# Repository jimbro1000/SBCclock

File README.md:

# Clock Card for HD6309SBC #

This board provides a variety of divided clock signals
to the 6809SBC board.

Where the SBC board calls for a quadrature clock (for
the 6809E variants) the board also provides Q and E.

The design is intended to be swappable to permit
easy exchange of different clock rates or different
clock generator designs.

The intended target is a raw clock of 25.175MHz to
facilitate a VGA signal. The CPU then operates at
one eighth of that - 3.15MHz, slightly above the
expected clock maximum for a C-class processor but
well within tolerance.

By having a swappable clock card the target 
operating frequency can be halved again to allow
the use of B-class processors while retaining
the 25MHz VGA signal. Again this is slightly
above specification at 1.57MHz but within the
tolerance of the design.

## Outputs ##

The card must provide the raw clock on Clock24, this
can be any frequency (that the CPUs support) but 
changing from the VGA clock frequency will require a
different approach to video output.

Outputs are then expected for the clock divided by
2, 4, 8 and 16 (Clock12, Clock6, Clock3 and Clock1.5)

Where Q and E are used they are output along with the
inverse of each.

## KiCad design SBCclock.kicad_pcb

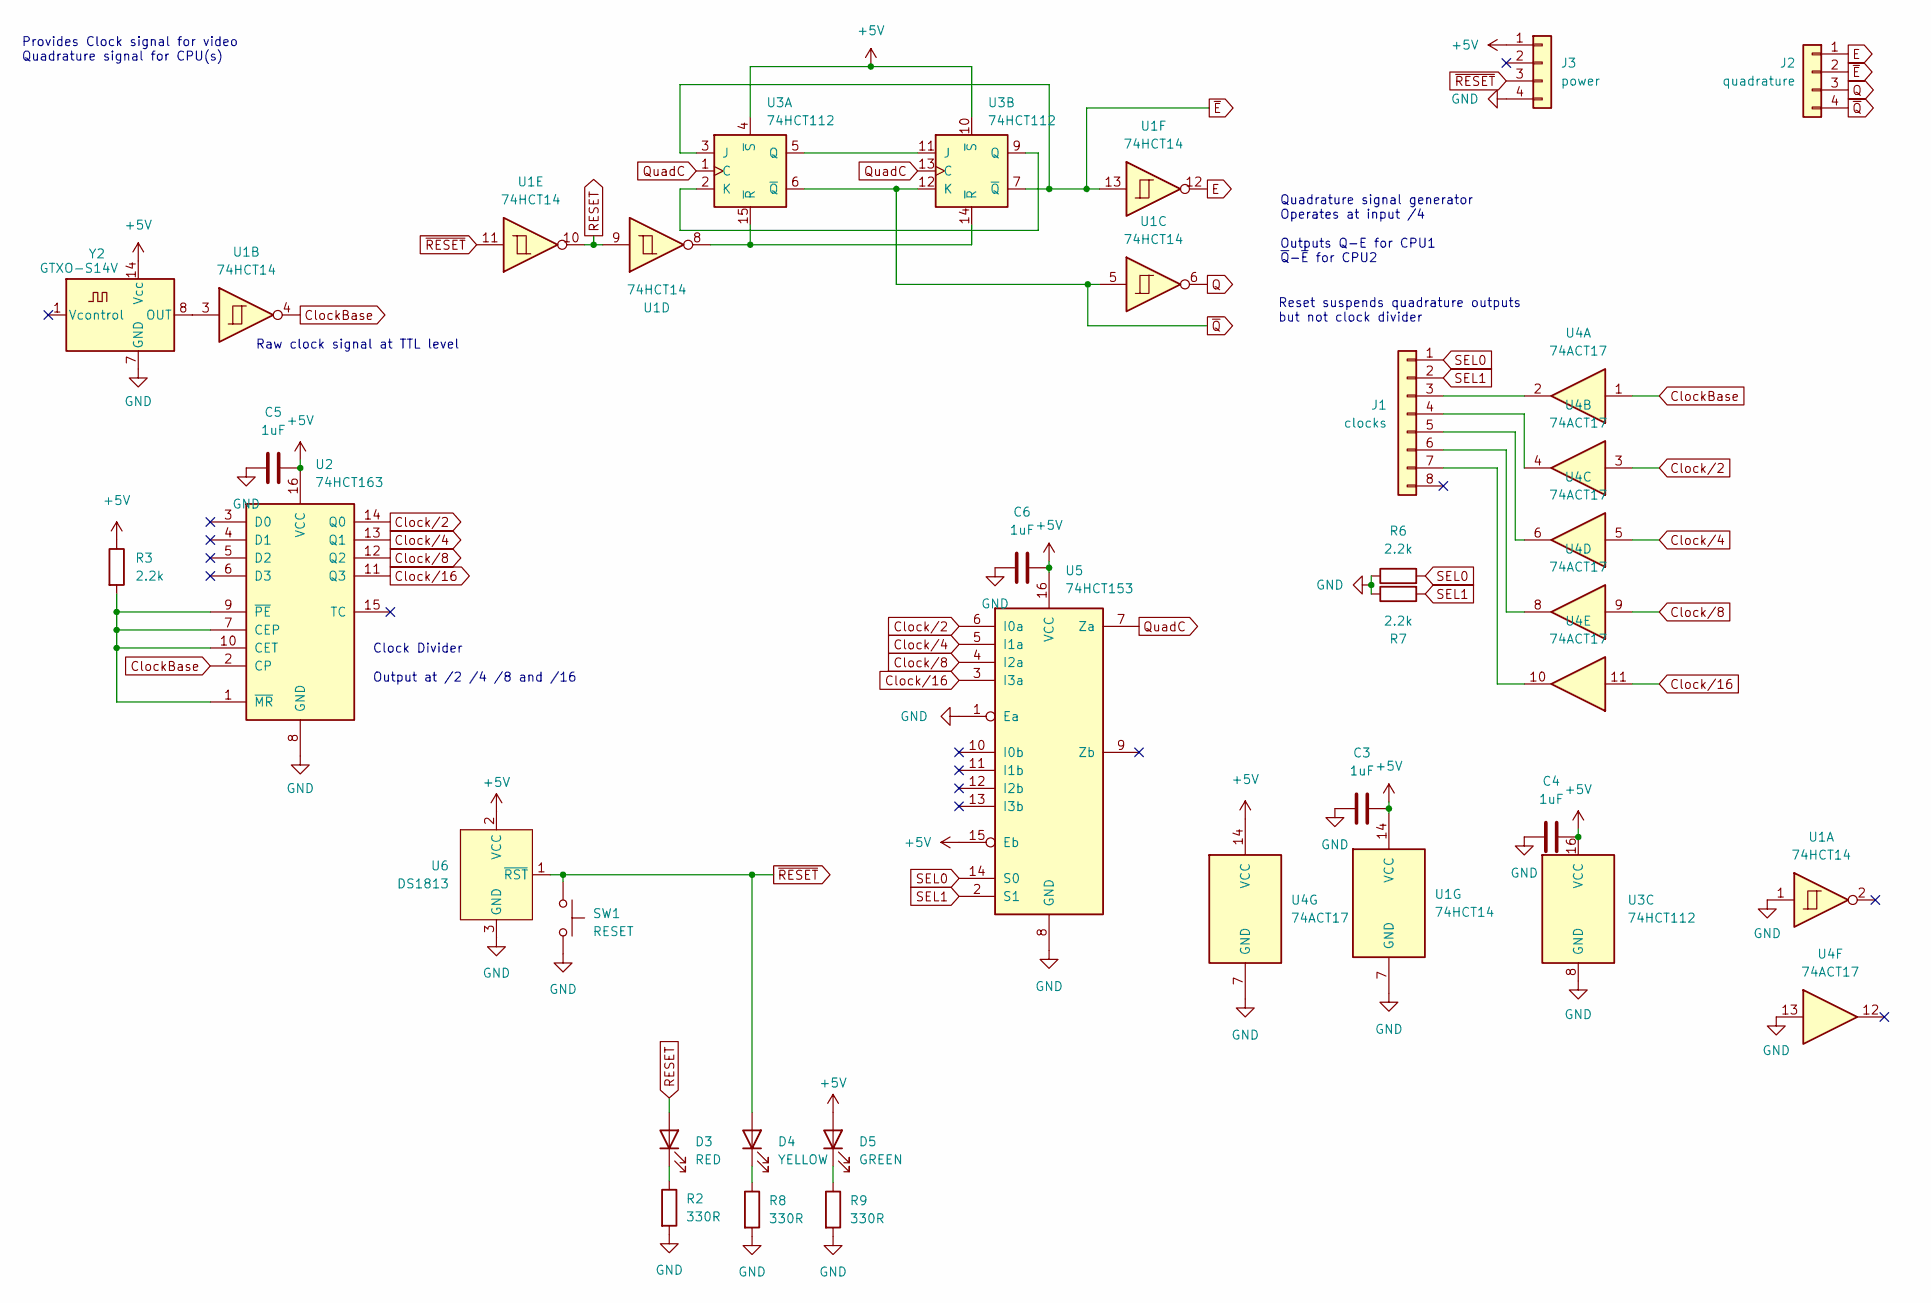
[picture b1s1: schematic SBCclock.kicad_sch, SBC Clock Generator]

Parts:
C3, C4, C5, C6: 1uF; C_0805_2012Metric_Pad1.18x1.45mm_HandSolder; DigiKey 4363-0805N180FW251XCT-ND
D3: RED; LED_0805_2012Metric_Pad1.15x1.40mm_HandSolder
D4: YELLOW; LED_0805_2012Metric_Pad1.15x1.40mm_HandSolder
D5: GREEN; LED_0805_2012Metric_Pad1.15x1.40mm_HandSolder
J1: clocks; PinHeader_1x08_P2.54mm_Vertical
J2: quadrature; PinHeader_1x04_P2.54mm_Vertical
J3: power; PinHeader_1x04_P2.54mm_Vertical
R2, R8, R9: 330R; R_0805_2012Metric_Pad1.20x1.40mm_HandSolder; DigiKey 2019-RK73H2ATTD2201FCT-ND
R3, R6, R7: 2.2k; R_0805_2012Metric_Pad1.20x1.40mm_HandSolder; DigiKey 2019-RK73H2ATTD2201FCT-ND
SW1: RESET; SW_SPST_B3S-1000
U1: 74HCT14; SOIC-14_3.9x8.7mm_P1.27mm; DigiKey 296-14864-1-ND
U2: 74HCT163; SOIC-16_3.9x9.9mm_P1.27mm; DigiKey 296-SN74HC163DTCT-ND
U3: 74HCT112; SOIC-16_3.9x9.9mm_P1.27mm; DigiKey 1727-74HCT112D,653CT-ND
U4: 74ACT17; TSSOP-14_4.4x5mm_P0.65mm; DigiKey 296-SN74ACT17PWRCT-ND
U5: 74HCT153; SOIC-16_3.9x9.9mm_P1.27mm; DigiKey 296-CD74HCT153M96CT-ND
U6: DS1813; SOT-23-3; DigiKey DS1813R-5+CT-ND
Y2: GTXO-S14V; Oscillator_DIP-8+14

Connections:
+5V: C3.1, C4.1, C5.1, C6.1, D5.2 (A), J3.1, R3.1, U1.14 (VCC), U2.16 (VCC), U3.4 (~S), U3.10 (~S), U3.16 (VCC), U4.14 (VCC), U5.15 (Eb), U5.16 (VCC), U6.2 (VCC), Y2.14 (Vcc)
ClockBase: U1.4, U2.2 (CP), U4.1
Clock/2: U2.14 (Q0), U4.3, U5.6 (I0a)
Clock/4: U2.13 (Q1), U4.5, U5.5 (I1a)
Clock/8: U2.12 (Q2), U4.9, U5.4 (I2a)
Clock/16: U2.11 (Q3), U4.11, U5.3 (I3a)
E: J2.1, U1.12
GND: C3.2, C4.2, C5.2, C6.2, J3.4, R2.2, R6.1, R7.1, R8.2, R9.2, SW1.2, U1.1, U1.7 (GND), U2.8 (GND), U3.8 (GND), U4.7 (GND), U4.13, U5.1 (Ea), U5.8 (GND), U6.3 (GND), Y2.7 (GND)
unnamed: D3.1 (K), R2.1
unnamed: D4.1 (K), R8.1
unnamed: D5.1 (K), R9.1
unnamed: J1.3, U4.2
unnamed: J1.4, U4.4
unnamed: J1.5, U4.6
unnamed: J1.6, U4.8
unnamed: J1.7, U4.10
unnamed: R3.2, U2.1 (~MR), U2.7 (CEP), U2.9 (~PE), U2.10 (CET)
unnamed: U3.2 (K), U3.9 (Q)
unnamed: U3.5 (Q), U3.11 (J)
unnamed: U1.8, U3.14 (~R), U3.15 (~R)
unnamed: U1.3, Y2.8 (OUT)
Q: J2.3, U1.6
QuadC: U3.1 (C), U3.13 (C), U5.7 (Za)
RESET: D3.2 (A), U1.9, U1.10
SEL0: J1.1, R6.2, U5.14 (S0)
SEL1: J1.2, R7.2, U5.2 (S1)
~E: J2.2, U1.13, U3.3 (J), U3.7 (~Q)
~Q: J2.4, U1.5, U3.6 (~Q), U3.12 (K)
~RESET: D4.2 (A), J3.3, SW1.1, U1.11, U6.1 (~RST)

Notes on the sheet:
Clock Divider Output at /2 /4 /8 and /16
Quadrature signal generator Operates at input /4 Outputs Q-E for CPU1 ~{Q}-~{E} for CPU2
Provides Clock signal for video Quadrature signal for CPU(s)
Reset suspends quadrature outputs but not clock divider
Raw clock signal at TTL level

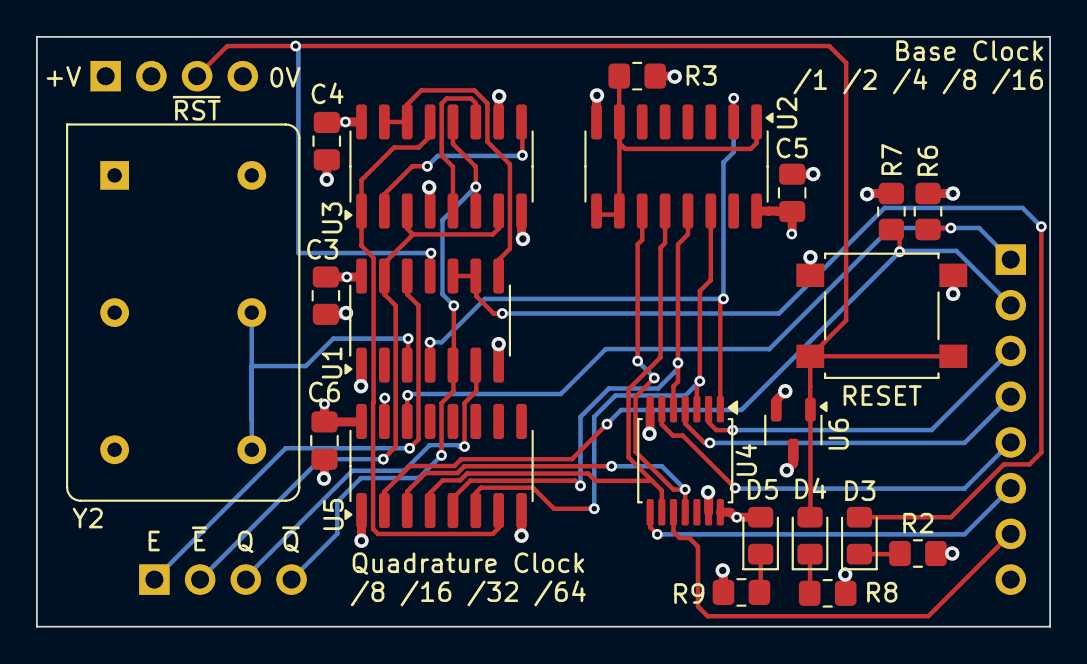
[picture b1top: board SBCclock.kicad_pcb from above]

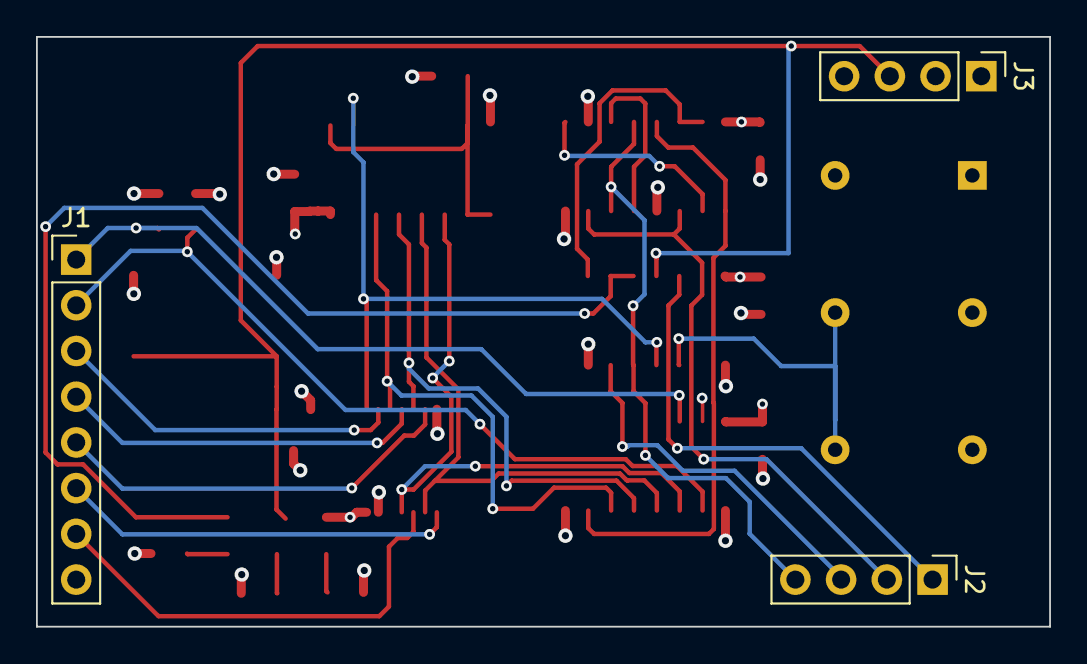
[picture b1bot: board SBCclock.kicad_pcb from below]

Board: 4 copper layers, 56.3 x 32.8 mm, 24 parts (3 on the bottom side), 29 nets.

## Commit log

2023-02-16 chore: tweak values
2023-02-16 chore: adjust routing
2023-02-16 refine for build
2023-03-07 revise E generation
2023-03-21 simplified board
2023-03-21 prepare for production
2023-08-04 revise clock signal
2024-05-14 v2 board
2024-05-14 revise load capacitors
2025-05-12 reinforce clock outputs
2025-06-12 revised board - tested
2025-06-12 remove redundant single gate
2026-03-09 refresh
2026-03-09 fix u4 footprint
